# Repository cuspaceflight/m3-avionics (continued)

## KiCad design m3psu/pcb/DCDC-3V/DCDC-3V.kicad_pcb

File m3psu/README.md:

# Martlet 3 Power Supply Unit

The Power Supply Unit is designed to have current monitoring and control over every single power line (5V, 3.3V, and VBatt), and all can be controlled via an MCU. It has on-board Li-ion battery charging and balancing capability, and can automatically switch between external power and internal power (or be commanded to do so).

## Notes By Module

### General Notes

- Everything is designed to assume shore power of 11.5V to 14.5V, i.e. a 12V lead-acid (car) battery.
- Internal power supply is assumed to be 2 Li-ion cells, 3.5V-4.2V per cell giving 7V-8.4V internal supply.
- All components are designed to function at max working voltage of 16V, or higher (usually 25V where possible).
- 0402s are not available for capacitors >1µF and ≥16V.
    - Large capacitors will have to use the smallest footprint possible (which varies accordingly).
- All resistors are 0402s unless carrying large currents. Check power rating (in hidden field) if so.
    - Be cautious about resistors with values <100Ω since they're likely carrying large enough currents to be concerned about power.
- Assembled stack has to have charger board and controller board next to each other, followed by DC/DC converters as furthest.
- The I2C Bus is pulled up at the microcontroller unit.

### DC/DC Converter

- Choose: LTC3887 2475658(FAR).
- Max current provisioned: 1A @5V or @3.3V
- Operating Frequency: 575kHz.
- Choose Schottky diode to carry 1A (these are optional in the circuit, but increases efficiency)(choose: NSR20F30NXT5G (2317558(FAR)).
- Switching pair of totem pole N-MOSFETs (choose: SiZ340DT (2422226(FAR)).
- Boost capacitors are 100x total input (gate) capacitance of topside MOSFETs.
- Bigger inductors are better, but it's a compromise on space (choose: TYS5040100M-10 2292532(FAR) -> Iripple = 0.41A).
- Large filtering capacitors give low ripple voltage. (choose: GRM21BR61E226ME44L 1907510(FAR) -> Vripple = 1.2mV).
- Rsense at 50mΩ because Vsense max is 75mV and expected current ~1A (choose: LRCS0603-0R05FT5 1506129(FAR)).
- Filter over Isense is 2\*Cp\*Rs ≤ ESL/R (equivalent series inductance of sense resistor est. ~0.5nH).

#### Software Configurations

- Addresses are 0x40 to 0x45 (0b100 0000 X to 0b100 0101 X), note that the EEPROM is supposed to have the 3 most significant bits as 100 by default.
    - Address 0x40:
        - V0 = 5V Cameras (1A)
        - V1 = 3.3V Pyro µC (0.1A)
    - Address 0x41:
        - V0 = 5V Radio AMP (0.35A)
        - V1 = 3.3V Radio µC + etc (0.25A)
    - Address 0x42:
        - V0 = 5V AUX1 (1A)
        - V1 = 5V CAN transceivers (0.1A)
    - Address 0x43:
        - V0 = 5V IMU ADIS (0.3A)
        - V1 = 3.3V IMU µC + etc (0.3A)
    - Address 0x44:
        - V0 = 5V AUX2 (1A)
        - V1 = 3.3V Flight Computer µC + etc (0.15A)
    - Address 0x45:
        - V0 = 3.3V AUX1 (1A)
        - V1 = 3.3V Datalogger µC + etc (0.3A)
- Since external temp monitoring is not needed and shorted to GND, set the `UT_FAULT_LIMIT` to –275°C, `IOUT_CAL_GAIN_TC` to zero and the `UT_FAULT_RE-SPONSE` to ignore.
- The DC/DC converters start low, and must be configured with their voltages before turning them on.
- Use `PAGE` command to select channel 0/1/both for control over I2C.
- Set `ON_OFF_CONFIG` to `On_off_config_use_pmbus`.
- Send `OPERATION` command to turn channel on or off as needed.

### Lithium Battery Charger

- Choose: MAX17435 2516688(FAR).
- Address is 0x09 (0b000 1001 X).
- Charging current limit is set to 2.7A using the potential divider, with assumption that cells are 2.6Ah.
- Switching pair of totem pole N-MOSFETs (choose: SiZ340DT (2422226(FAR)), same as in the DC/DC Converter.
- The P-FET from the battery needs to have *very low* Rds-on for efficiency (choose: Si7157DP 2471947(FAR) it's big, but there's nothing smaller).
- P-FET from main power just needs to have low enough Rds-on to handle ~4A (choose: Si7101DN 2364059(FAR)). This is used to control whether the charger is actually charging.
- The two soft-start N-MOSFETs on the input need to withstand 3A current draw (choose: STL15DN4F5 2098274(FAR) it's also big, but is a pair).
- The reverse polarity protection(?) N-MOSFET can be as small as possible since it carries very little current (choose: PMZB150UNE 2498598(FAR)).
- Big inductor is needed for lower ripple current for more efficiency (choose: SRP5030T-4R7M 2309887(FAR) -> Iripple = 0.9A).
- Large input and output capacitance to stabilise circuit (choose: GRM32ER61C476ME15L 1735538(FAR)).
- ACIN limits are 11.5-14.5V using the potential divider, with assumption of a nominal source charging of 12V (lead-acid battery).

#### Software Considerations

- The charger has two "switches", one for enabling charging and monitoring of discharging, and the other to control if the charger is connected to the external power supply.
- By default, both are pulled down, and so must be set high for charging to begin.
- When switching from shore power to internal power before launch, disable the external power supply from the charger first, and then switch the whole stack using the dedicated power OR.
    - The reason is because the Lithium Charger does its *own* power OR-ing but isn't as fast, so just switching from the dedicated power OR causes the lithium charger to switch at the same time, causing the switchover time to be the slower of the 2 which is undesirable, and pointless.
- All digital inputs and outputs (apart from the Bus) are funneled through the port expander (see port expander for details).

##### Port Expander (for Lithium Charger)

- Choose: PCAL9538A 2428172(FAR).
- Address is 0x70 (0b111 0000 X).
- Ports P4-P7 are grounded to prevent floating, but datasheet advises to change them to outputs after bootup.

### Lithium Battery Bleeders

- The N-MOSFETs carries only small amounts of current and so can be very small (choose: PMZB150UNE 2498598(FAR)).
- The P-MOSFET carries only a small amount of current and so can be very small (choose: PMZB320UPE 2498601(FAR)).
- The bleed resistors have to take around 0.5W if they are 47Ω (choose: ERJP06F47R0V 1750737(FAR)).

### Lithium Battery Module

- This will use one of the global reserve lines for the middle battery tap, but will not be linked to the external lines. Note that this will break the global interconnection.

### Active Power ORing

- Choose: LTC4353 2115909(FAR).
- N-MOSFETs need to withstand 3A current draw (choose: STL15DN4F5 2098274(FAR)), same as in Lithium Battery Charger.
- Capacitors 10x the gate capacitance (Ciss) of the MOSFET that it is switching (choose: CGA2B3X7R1H223K050BB 2210825(FAR)).

### Pyro Channel Monitor and Control

- Choose: LTC4151 (2295457(FAR)).
- The P-MOSFETs that control the channel have to carry up to 2A each for short bursts (choose: CSD25310Q2 2501102(FAR)).
- The N-MOSFET that control the P-MOSFET only carries a small amount of current (choose: PMZB150UNE 2498598(FAR)), same as the Li-ion bleeders.

#### Software Configurations

- Address of Current Monitor is 0x6F (0b110 1111 X).
- The readout for the current is 0-81.92mV (20µV resolution) and must be converted to mA. With Rsense = 0.01Ω, range is 0-8A, with resolution of 2mA.
- The readout of the voltage is also the readout of the main line voltage (after the power OR).

### PSU for the PSU

- Choose: TPS61252 2382918(FAR).
- Max current provisioned: 0.2A @3.3V.
- Operatiing frequency: 1.25MHz.
- Choose smallest footprint inductor possible which meets requirements (choose: VLS201610HBX-3R3M-1 2455353(FAR)).
- Input-Output Capacitors are large for low ripple (choose: GRM21BR61E226ME44L 1907510(FAR)).

## List of Common Parts

### Capacitors (25V)

- 4µ7 - 2426959
- 1µ - 2218855

- 100n - 2496811

- 10n - 2210793

- 4n7 - 2496786
- 1n5 - 2210833

- 220p - 2210772
- 47p - 2210781

### Resistors (±1%)

- 2M - 1458762

- 150k - 2447110
- 100k - 2447094

- 56k - 2447198
- 33k - 2447160
- 30k1 - 2072900
- 24k9 - 1803690
- 23k2 - 2302774
- 15k8 - 2302757
- 10k - 2447096

- 7k32 - 2073231
- 6k2 - 2331559
- 5k76 - 1803113
- 5k1 - 2447201
- 4k99 - 1469715
- 4k7 - 2447187
- 4k32 - 2073037
- 3k57 - 2302693
- 1k96 - 1803065
- 1k - 2447120

- 100 - 2447095

- 50m - 1506129

## Notes on Routing

### Microcontroller Board

- I2C pins on:
    - 40,41,42 (SDA,SCL,SMBA) I2C(3)
    - 57,58,59 (SMBA,SCL,SDA) I2C(1)
    - 29,30,33 (SCL,SDA,SMBA) I2C(2)
- The various GPIOs have not been connected in the schematic yet, and hence will not show up on the routing. Route them last, since any GPIO port works.
- The bottom and left side of the microcontroller is mostly inaccessible using this layout.
- Note that the DCDC converter (3v3) operates at 1.25MHz, so keep it away from signal channels, and keep the components as tight as possible together.
- Shift the power OR a little more to the left (leave some room for the logic tracks). The top left dual MOSFET can go closer to the connector and northwards. The other dual MOSFET needs to be shifted down a little and left.
- VSHORE from the dual MOSFET should not cut across the large empty space on the right. (makes other things difficult to fit)

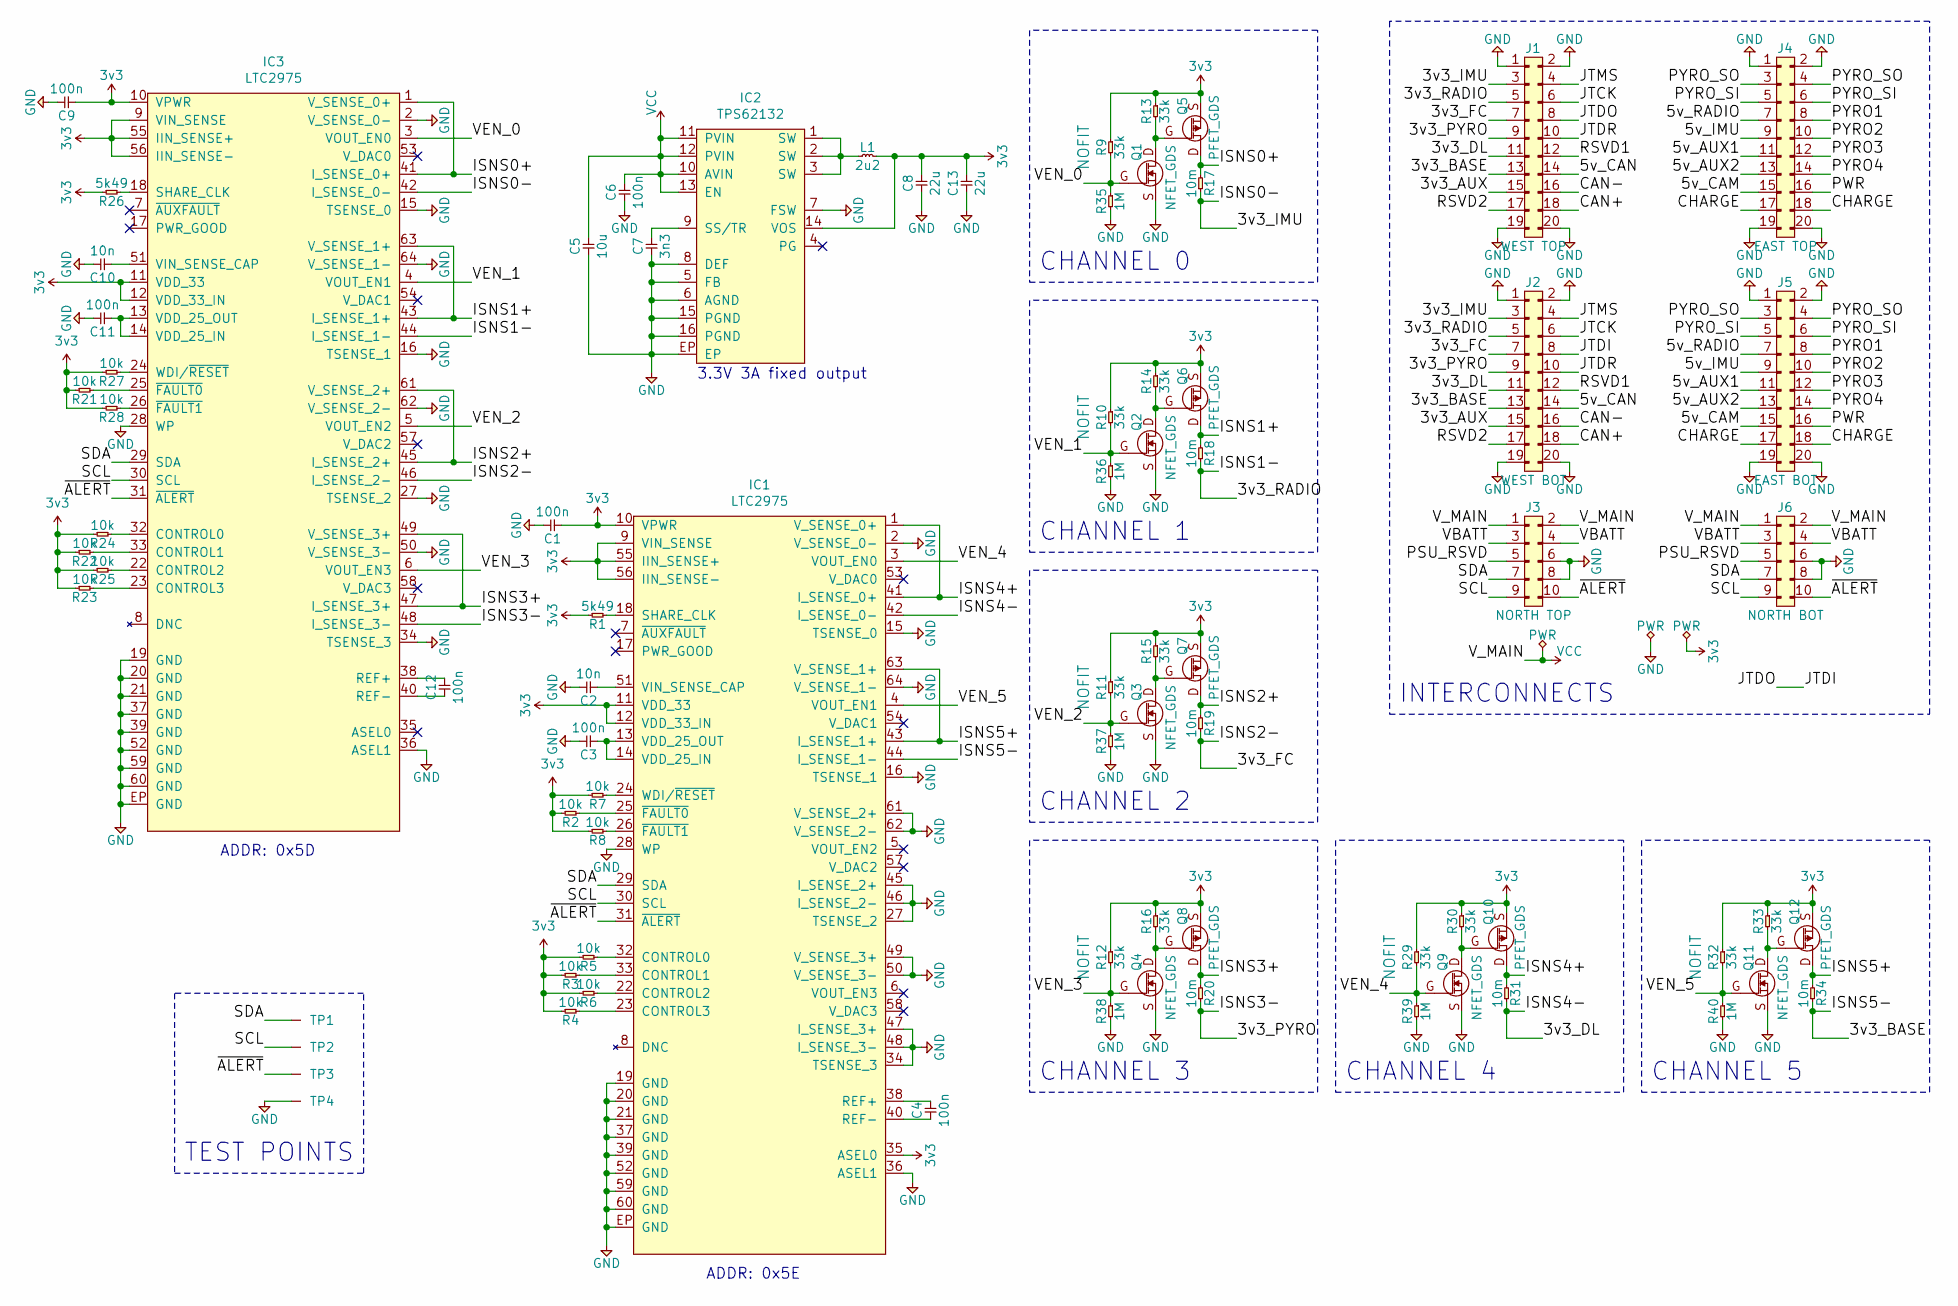
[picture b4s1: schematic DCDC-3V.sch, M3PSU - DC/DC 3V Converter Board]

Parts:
C1, C3, C4, C6, C9, C11, C12: 100n; 0402
C2, C10: 10n; 0402
C5: 10u; 0805
C7: 3n3; 0402
C8, C13: 22u; 0805
IC1, IC3: LTC2975; QFN-64-EP-LTC-UP; Farnell 2461150
IC2: TPS62132; QFN-16-EP-TI; Farnell 2492468
J1: WEST TOP; TFML-110-02-L-D
J2: WEST BOT; SFML-110-02-L-D-LC
J3: NORTH TOP; TFML-105-02-L-D
J4: EAST TOP; TFML-110-02-L-D
J5: EAST BOT; SFML-110-02-L-D-LC
J6: NORTH BOT; SFML-105-02-L-D-LC
L1: 2u2; XFL4020; Farnell 2289216
Q1, Q2, Q3, Q4, Q9, Q11: NFET_GDS; PowerPAK-SC-75-6L-Single; Farnell 2364070
Q5, Q6, Q7, Q8, Q10, Q12: PFET_GDS; SON2x2; Farnell 2501102
R1, R26: 5k49; 0402
R2, R3, R4, R5, R6, R7, R8, R21, R22, R23, R24, R25, R27, R28: 10k; 0402
R9, R10, R11, R12, R13, R14, R15, R16, R29, R30, R32, R33: 33k; 0402
R17, R18, R19, R20, R31, R34: 10m; 0603
R35, R36, R37, R38, R39, R40: 1M; 0402
TP1, TP2, TP3, TP4: TESTPAD

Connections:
3v3: C1.2, C8.1, C9.2, C13.1, IC1.9 (VIN_SENSE), IC1.10 (VPWR), IC1.11 (VDD_33), IC1.12 (VDD_33_IN), IC1.35 (ASEL0), IC1.55 (IIN_SENSE+), IC1.56 (IIN_SENSE-), IC2.14 (VOS), IC3.9 (VIN_SENSE), IC3.10 (VPWR), IC3.11 (VDD_33), IC3.12 (VDD_33_IN), IC3.55 (IIN_SENSE+), IC3.56 (IIN_SENSE-), L1.2, Q5.S, Q6.S, Q7.S, Q8.S, Q10.S, Q12.S, R1.1, R2.1, R3.1, R4.1, R5.1, R6.1, R7.1, R8.1, R9.1, R10.1, R11.1, R12.1, R13.1, R14.1, R15.1, R16.1, R21.1, R22.1, R23.1, R24.1, R25.1, R26.1, R27.1, R28.1, R29.1, R30.1, R32.1, R33.1
/3v3_AUX: J1.15, J2.15
/3v3_BASE: IC1.44 (I_SENSE_1-), J1.13, J2.13, R34.1
/3v3_DL: IC1.42 (I_SENSE_0-), J1.11, J2.11, R31.1
/3v3_FC: IC3.46 (I_SENSE_2-), J1.7, J2.7, R19.1
/3v3_IMU: IC3.42 (I_SENSE_0-), J1.3, J2.3, R17.1
/3v3_PYRO: IC3.48 (I_SENSE_3-), J1.9, J2.9, R20.1
/3v3_RADIO: IC3.44 (I_SENSE_1-), J1.5, J2.5, R18.1
/5v_AUX1: J4.11, J5.11
/5v_AUX2: J4.13, J5.13
/5v_CAM: J4.15, J5.15
/5v_CAN: J1.14, J2.14
/5v_IMU: J4.9, J5.9
/5v_RADIO: J4.7, J5.7
/CAN+: J1.18, J2.18
/CAN-: J1.16, J2.16
/CHARGE: J4.17, J4.18, J5.17, J5.18
/ISNS0+: IC3.1 (V_SENSE_0+), IC3.41 (I_SENSE_0+), Q5.D, R17.2
/ISNS1+: IC3.43 (I_SENSE_1+), IC3.63 (V_SENSE_1+), Q6.D, R18.2
/ISNS2+: IC3.45 (I_SENSE_2+), IC3.61 (V_SENSE_2+), Q7.D, R19.2
/ISNS3+: IC3.47 (I_SENSE_3+), IC3.49 (V_SENSE_3+), Q8.D, R20.2
/ISNS4+: IC1.1 (V_SENSE_0+), IC1.41 (I_SENSE_0+), Q10.D, R31.2
/ISNS5+: IC1.43 (I_SENSE_1+), IC1.63 (V_SENSE_1+), Q12.D, R34.2
/JTCK: J1.6, J2.6
/JTDI: J1.8, J2.8
/JTDR: J1.10, J2.10
/JTMS: J1.4, J2.4
/PSU_RSVD: J3.5, J6.5
/PWR: J4.16, J5.16
/PYRO1: J4.8, J5.8
/PYRO2: J4.10, J5.10
/PYRO3: J4.12, J5.12
/PYRO4: J4.14, J5.14
/PYRO_SI: J4.5, J4.6, J5.5, J5.6
/PYRO_SO: J4.3, J4.4, J5.3, J5.4
/RSVD1: J1.12, J2.12
/RSVD2: J1.17, J2.17
/SCL: IC1.30 (SCL), IC3.30 (SCL), J3.9, J6.9, TP2.1
/SDA: IC1.29 (SDA), IC3.29 (SDA), J3.7, J6.7, TP1.1
/VBATT: J3.3, J3.4, J6.3, J6.4
/VEN_0: IC3.3 (VOUT_EN0), Q1.G, R9.2, R35.1
/VEN_1: IC3.4 (VOUT_EN1), Q2.G, R10.2, R36.1
/VEN_2: IC3.5 (VOUT_EN2), Q3.G, R11.2, R37.1
/VEN_3: IC3.6 (VOUT_EN3), Q4.G, R12.2, R38.1
/VEN_4: IC1.3 (VOUT_EN0), Q9.G, R29.2, R39.1
/VEN_5: IC1.4 (VOUT_EN1), Q11.G, R32.2, R40.1
/~ALERT: IC1.31 (~ALERT), IC3.31 (~ALERT), J3.10, J6.10, TP3.1
GND: C1.1, C2.1, C3.1, C5.2, C6.2, C7.2, C8.2, C9.1, C10.1, C11.1, C13.2, IC1.2 (V_SENSE_0-), IC1.15 (TSENSE_0), IC1.16 (TSENSE_1), IC1.19 (GND), IC1.20 (GND), IC1.21 (GND), IC1.27 (TSENSE_2), IC1.28 (WP), IC1.34 (TSENSE_3), IC1.36 (ASEL1), IC1.37 (GND), IC1.39 (GND), IC1.45 (I_SENSE_2+), IC1.46 (I_SENSE_2-), IC1.47 (I_SENSE_3+), IC1.48 (I_SENSE_3-), IC1.49 (V_SENSE_3+), IC1.50 (V_SENSE_3-), IC1.52 (GND), IC1.59 (GND), IC1.60 (GND), IC1.61 (V_SENSE_2+), IC1.62 (V_SENSE_2-), IC1.64 (V_SENSE_1-), IC1.EP (GND), IC2.5 (FB), IC2.6 (AGND), IC2.7 (FSW), IC2.8 (DEF), IC2.15 (PGND), IC2.16 (PGND), IC2.EP, IC3.2 (V_SENSE_0-), IC3.15 (TSENSE_0), IC3.16 (TSENSE_1), IC3.19 (GND), IC3.20 (GND), IC3.21 (GND), IC3.27 (TSENSE_2), IC3.28 (WP), IC3.34 (TSENSE_3), IC3.36 (ASEL1), IC3.37 (GND), IC3.39 (GND), IC3.50 (V_SENSE_3-), IC3.52 (GND), IC3.59 (GND), IC3.60 (GND), IC3.62 (V_SENSE_2-), IC3.64 (V_SENSE_1-), IC3.EP (GND), J1.1, J1.2, J1.19, J1.20, J2.1, J2.2, J2.19, J2.20, J3.6, J3.8, J4.1, J4.2, J4.19, J4.20, J5.1, J5.2, J5.19, J5.20, J6.6, J6.8, Q1.S, Q2.S, Q3.S, Q4.S, Q9.S, Q11.S, R35.2, R36.2, R37.2, R38.2, R39.2, R40.2, TP4.1
unnamed: C2.2, IC1.51 (VIN_SENSE_CAP)
unnamed: C3.2, IC1.13 (VDD_25_OUT), IC1.14 (VDD_25_IN)
unnamed: C4.1, IC1.38 (REF+)
unnamed: C4.2, IC1.40 (REF-)
unnamed: C7.1, IC2.9 (SS/TR)
unnamed: C10.2, IC3.51 (VIN_SENSE_CAP)
unnamed: C11.2, IC3.13 (VDD_25_OUT), IC3.14 (VDD_25_IN)
unnamed: C12.1, IC3.38 (REF+)
unnamed: C12.2, IC3.40 (REF-)
unnamed: IC1.18 (SHARE_CLK), R1.2
unnamed: IC1.22 (CONTROL2), R6.2
unnamed: IC1.23 (CONTROL3), R4.2
unnamed: IC1.24 (WDI/~RESET), R7.2
unnamed: IC1.25 (~FAULT0), R2.2
unnamed: IC1.26 (~FAULT1), R8.2
unnamed: IC1.32 (CONTROL0), R5.2
unnamed: IC1.33 (CONTROL1), R3.2
unnamed: IC2.1 (SW), IC2.2 (SW), IC2.3 (SW), L1.1
unnamed: IC3.18 (SHARE_CLK), R26.2
unnamed: IC3.22 (CONTROL2), R25.2
unnamed: IC3.23 (CONTROL3), R23.2
unnamed: IC3.24 (WDI/~RESET), R27.2
unnamed: IC3.25 (~FAULT0), R21.2
unnamed: IC3.26 (~FAULT1), R28.2
unnamed: IC3.32 (CONTROL0), R24.2
unnamed: IC3.33 (CONTROL1), R22.2
unnamed: Q1.D, Q5.G, R13.2
unnamed: Q2.D, Q6.G, R14.2
unnamed: Q3.D, Q7.G, R15.2
unnamed: Q4.D, Q8.G, R16.2
unnamed: Q9.D, Q10.G, R30.2
unnamed: Q11.D, Q12.G, R33.2
VCC: C5.1, C6.1, IC2.10 (AVIN), IC2.11 (PVIN), IC2.12 (PVIN), IC2.13 (EN), J3.1, J3.2, J6.1, J6.2

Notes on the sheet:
INTERCONNECTS
ADDR: 0x5E
CHANNEL 0
CHANNEL 1
CHANNEL 2
CHANNEL 3
3.3V 3A fixed output
CHANNEL 4
CHANNEL 5
ADDR: 0x5D
TEST POINTS

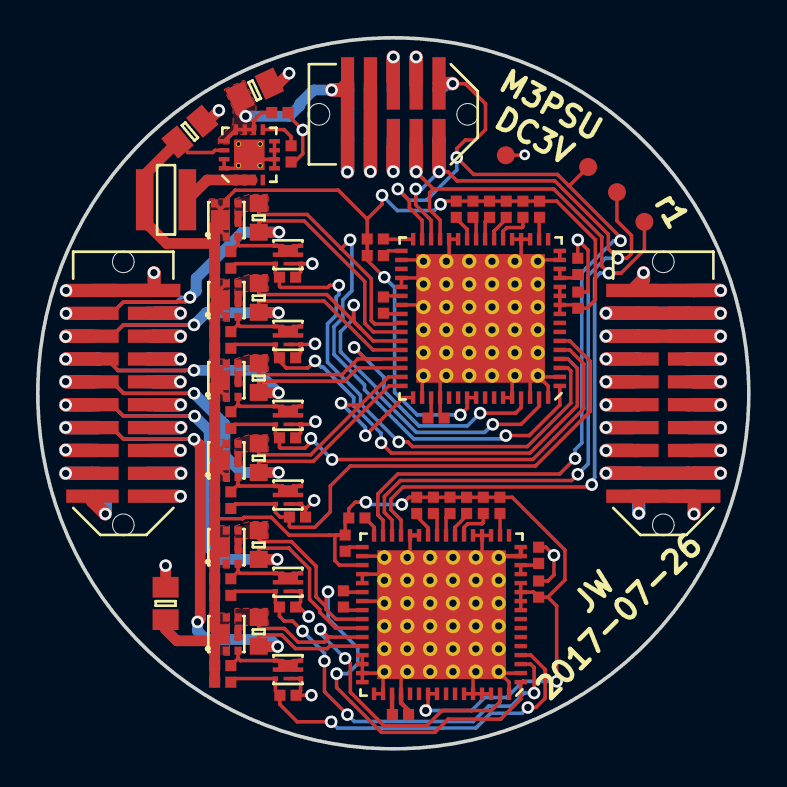
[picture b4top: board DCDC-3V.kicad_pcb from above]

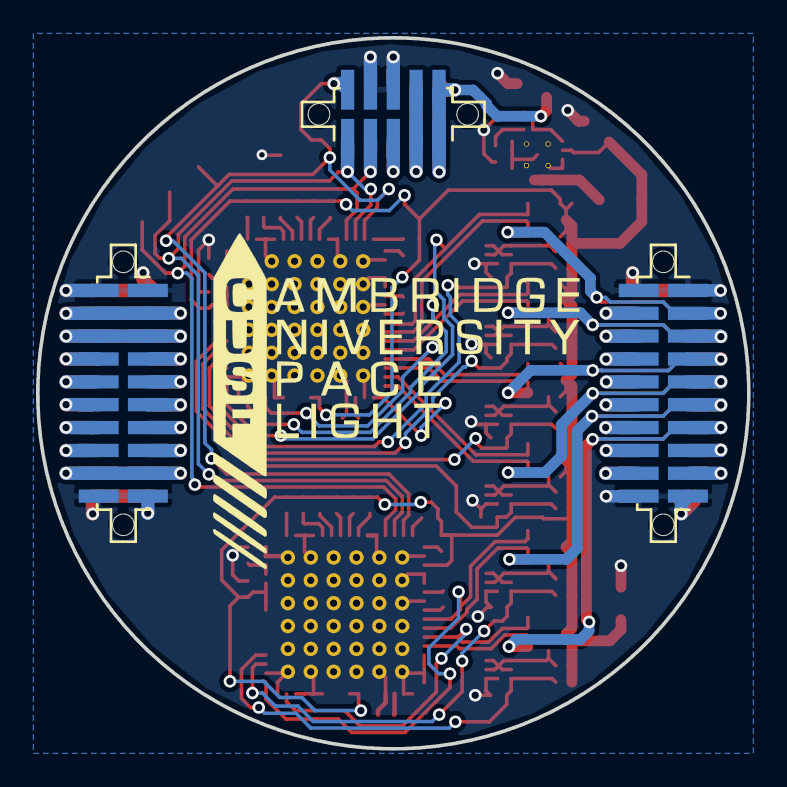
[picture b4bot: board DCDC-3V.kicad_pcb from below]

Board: 2 copper layers, 39.5 x 39.5 mm, 79 parts (3 on the bottom side), 81 nets.

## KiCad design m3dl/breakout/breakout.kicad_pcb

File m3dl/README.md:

# Martlet 3 Data Logger Stack

For overall BOM see: http://bit.ly/1YytYK4

x1 Temperature Sensor Board:
- LTC2983 10 Channel fancy box.
- 9 Thermocouples w/ Cold junction compensation.
- SPI over data logger stack interconnect (x4 Pins) plus interrupt.
- On board 18-pin connector (2 Pins per Thermocouple) connects to a wiring harness which passes through cutouts in below boards and breaks out to 9x 2-Pin in line connectors for thermocouples.

x2 Strain Gauge Boards:
- Analogue front end w/ AD8226.
- 3 Strain Gauges per PCB – 6 Total.
- Connection to ADC Inputs over data logger stack interconnect (x6 Pins).
- Per PCB 3 on board 4-pin connectors (1 per Gauge) connect to a wiring harness which passes through cutouts in below boards and breaks out to 6x 4-Pin in line connectors for strain gauges.

x1 Pressure Sensor Board:
- Absolute pressure sensors with mV Output to be placed externally.
- Simple RC filter connects sensor outputs to ADC over data logger stack interconnect (x5 Pins).
- Maximum 5 external Pressure Sensors .
- On board 10-pin connector to a cable which passes through cutouts in below boards and attaches to the external sensors through a wiring harness in a similar manner to the above.

x1 Main Board:
- 64 Pin STM32F405
- uSD Card
- CAN Controller
- Surface mount USB port for debugging

x1 Base JTAG & Connector Board:
- STM32F4 doing JTAG to USB and CAN to USB simultaneous
- JST-PA Connectors for USB, Pyro, Power/Charge, ARM and CAMERA.

20 Pin Data Logger Interconnect: 
 - x5 SPI 
 - x5 ADC Pressure 
 - x6 ADC Strain 
 - x4 GND

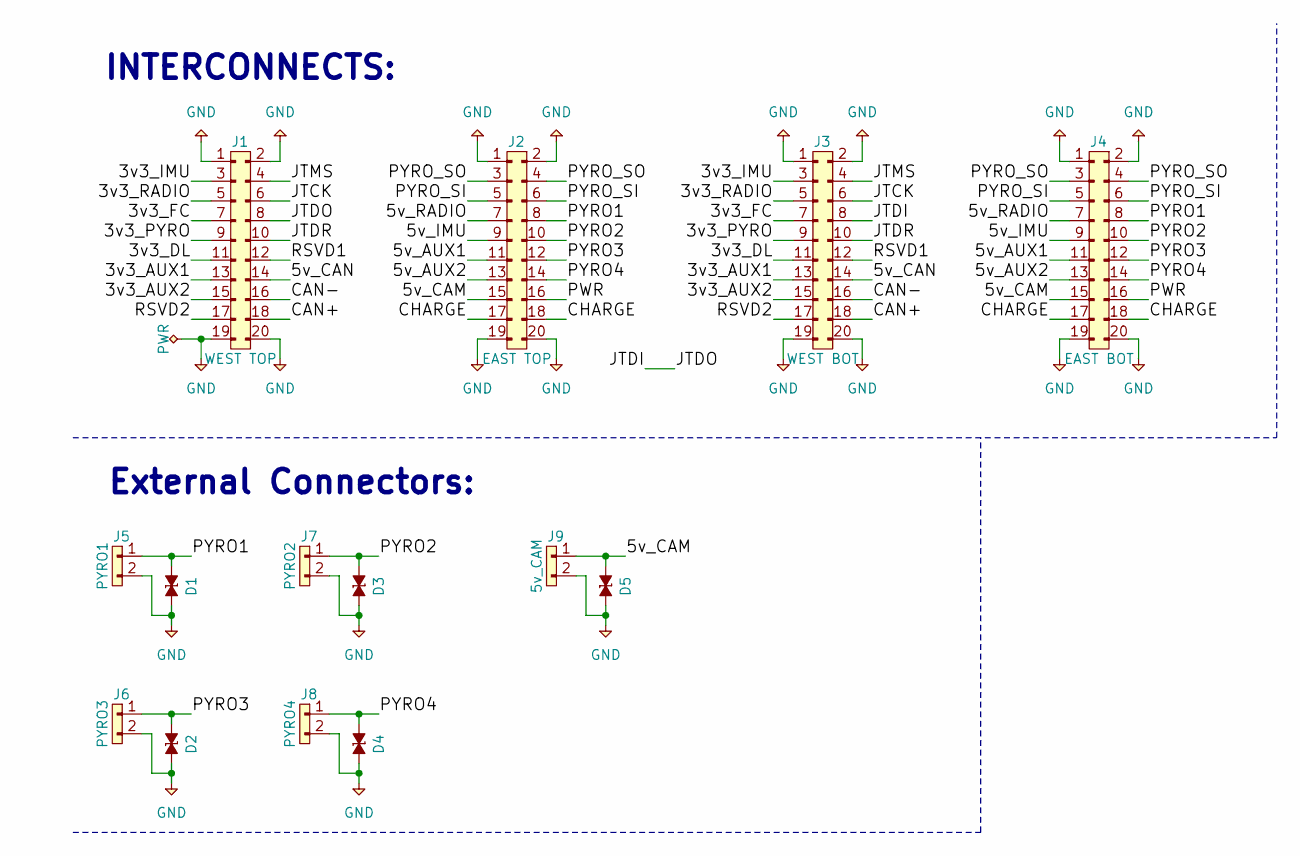
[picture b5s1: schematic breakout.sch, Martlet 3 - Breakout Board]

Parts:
D1, D2, D3, D4, D5: ESD_DIODE; 0402; Farnell 2368169
J1: WEST TOP; TFML-110-02-L-D
J2: EAST TOP; TFML-110-02-L-D
J3: WEST BOT; SFML-110-02-L-D-LC
J4: EAST BOT; SFML-110-02-L-D-LC
J5: PYRO1; S2B-EH
J6: PYRO3; S2B-EH
J7: PYRO2; S2B-EH
J8: PYRO4; S2B-EH
J9: 5v_CAM; S2B-EH

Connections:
/3v3_AUX1: J1.13, J3.13
/3v3_AUX2: J1.15, J3.15
/3v3_DL: J1.11, J3.11
/3v3_FC: J1.7, J3.7
/3v3_IMU: J1.3, J3.3
/3v3_PYRO: J1.9, J3.9
/3v3_RADIO: J1.5, J3.5
/5v_AUX1: J2.11, J4.11
/5v_AUX2: J2.13, J4.13
/5v_CAM: D5.1, J2.15, J4.15, J9.1
/5v_CAN: J1.14, J3.14
/5v_IMU: J2.9, J4.9
/5v_RADIO: J2.7, J4.7
/CAN+: J1.18, J3.18
/CAN-: J1.16, J3.16
/CHARGE: J2.17, J2.18, J4.17, J4.18
/JTCK: J1.6, J3.6
/JTDI: J1.8, J3.8
/JTDR: J1.10, J3.10
/JTMS: J1.4, J3.4
/PWR: J2.16, J4.16
/PYRO1: D1.1, J2.8, J4.8, J5.1
/PYRO2: D3.1, J2.10, J4.10, J7.1
/PYRO3: D2.1, J2.12, J4.12, J6.1
/PYRO4: D4.1, J2.14, J4.14, J8.1
/PYRO_SI: J2.5, J2.6, J4.5, J4.6
/PYRO_SO: J2.3, J2.4, J4.3, J4.4
/RSVD1: J1.12, J3.12
/RSVD2: J1.17, J3.17
GND: D1.2, D2.2, D3.2, D4.2, D5.2, J1.1, J1.2, J1.19, J1.20, J2.1, J2.2, J2.19, J2.20, J3.1, J3.2, J3.19, J3.20, J4.1, J4.2, J4.19, J4.20, J5.2, J6.2, J7.2, J8.2, J9.2

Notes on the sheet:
INTERCONNECTS:
External Connectors:

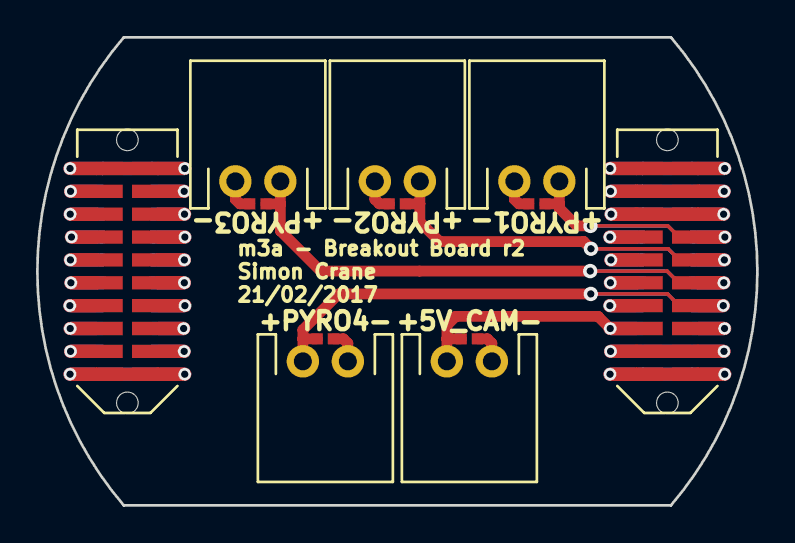
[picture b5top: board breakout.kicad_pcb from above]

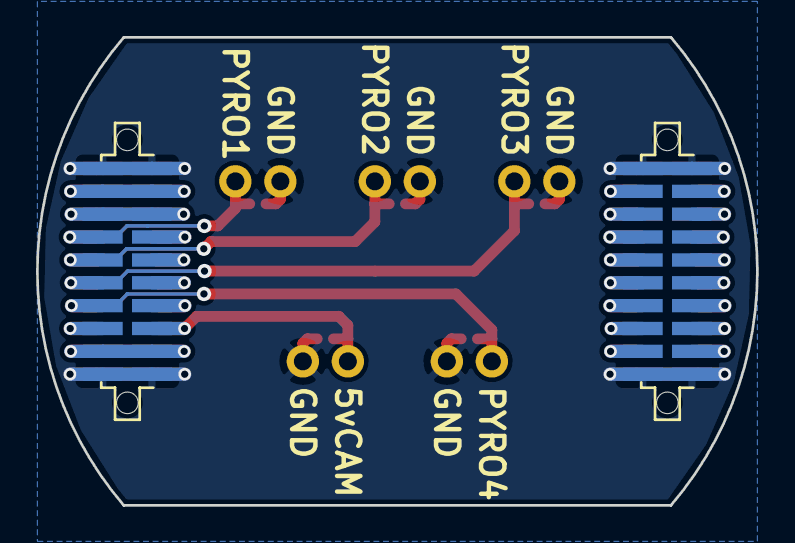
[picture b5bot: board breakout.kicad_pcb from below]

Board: 2 copper layers, 40.0 x 26.0 mm, 14 parts (2 on the bottom side), 30 nets.

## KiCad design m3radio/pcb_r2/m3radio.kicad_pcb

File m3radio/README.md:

# Martlet 3 Radio

Datasheets:
[GPS ublox max-7q]: https://www.u-blox.com/sites/default/files/products/documents/MAX7-NEO7_HIM_(UBX-13003704).pdf
[Radio SI4460]: https://www.silabs.com/Support%20Documents/TechnicalDocs/Si4464-63-61-60.pdf

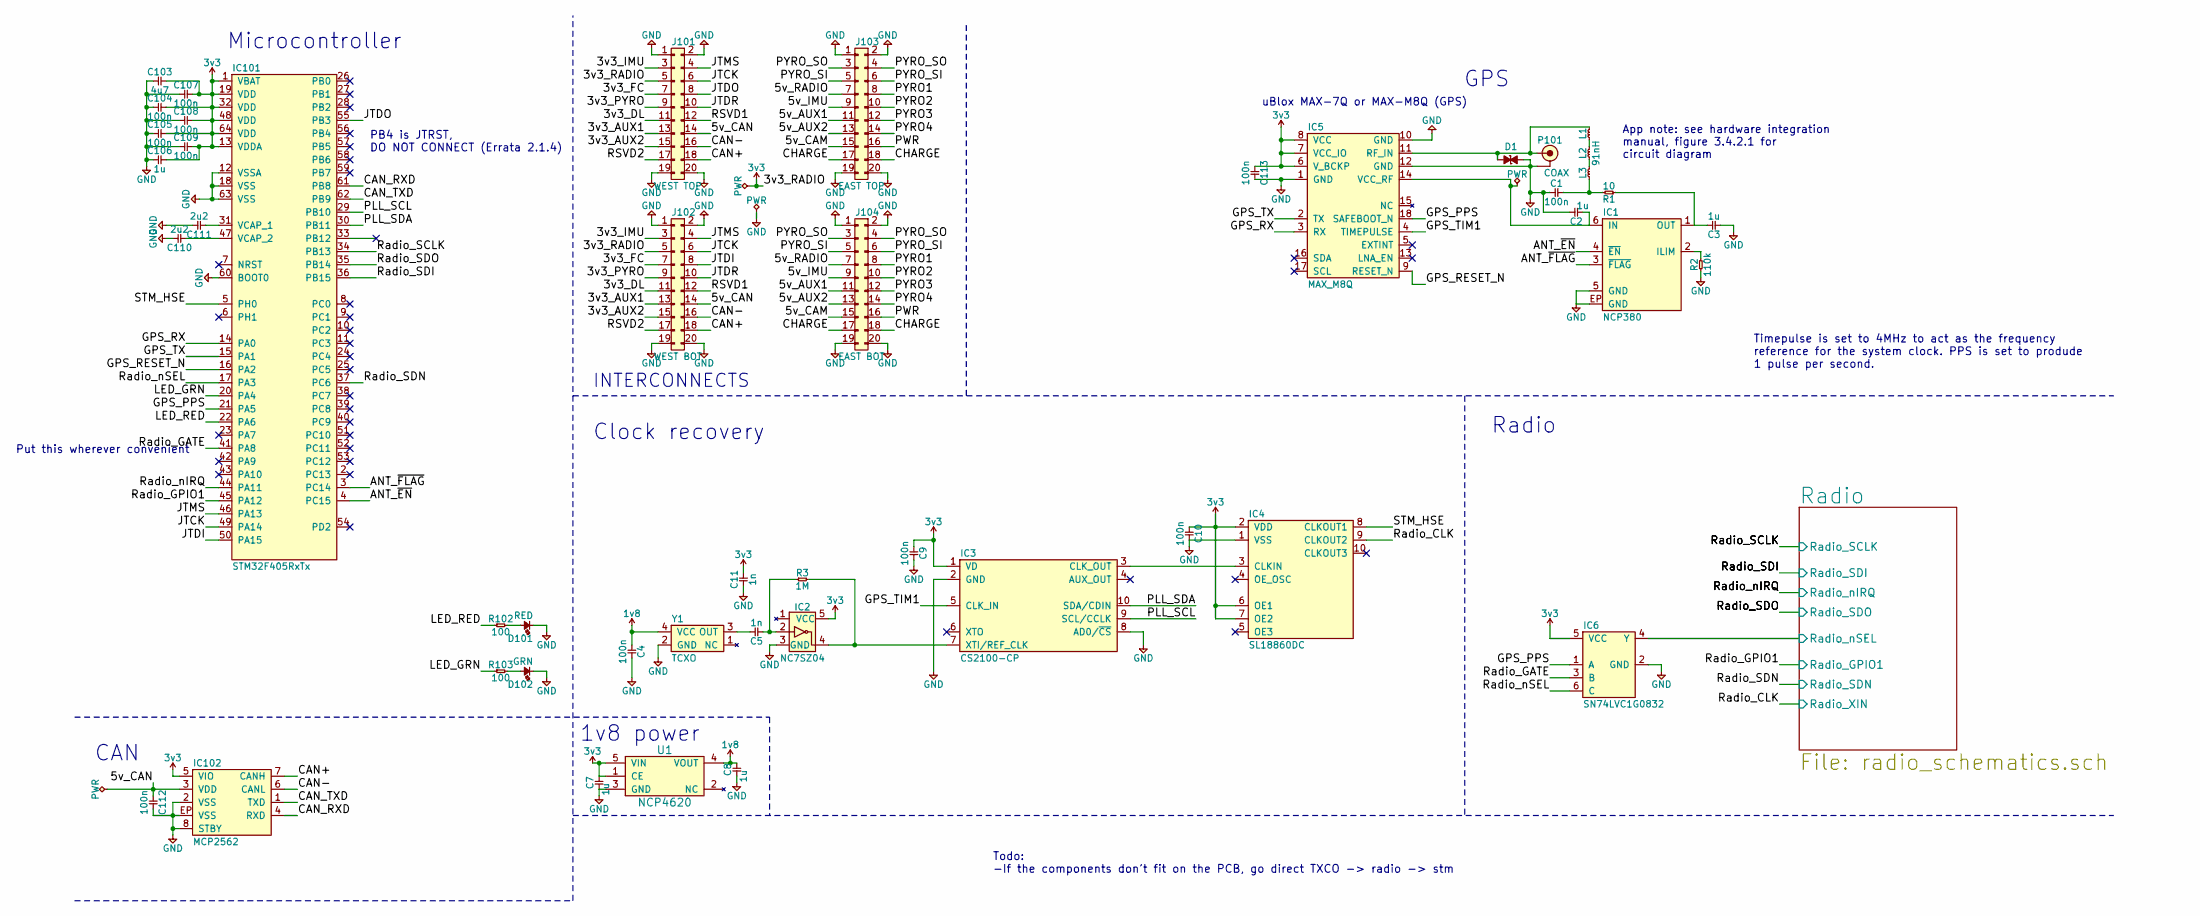
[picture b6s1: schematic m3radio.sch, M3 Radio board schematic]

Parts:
C1, C4, C9, C10, C104, C105, C107, C108, C109, C112, C113: 100n; 0402; Farnell 2496771
C2, C3, C7, C8, C106: 1u; 0402; Farnell 2496814
C5, C11: 1n; 0402; Farnell 2495166
C103: 4u7; 0402; Farnell 2426952
C110, C111: 2u2; 0402; Farnell 2362088
D1: ESD_DIODE; 0402; Farnell 2368169
D101: RED; 0603-LED; Farnell 2314404
D102: GRN; 0603-LED; Farnell 2290363
IC1: NCP380; DFN-6-EP-ONSEMI; Farnell 2464412
IC2: NC7SZ04; SOT-23-5; Farnell 1417667
IC3: CS2100-CP; MSOP-10; Mouser 777-CS2100CP-CZZ
IC4: SL18860DC; DFN-10-SL18860DC; Mouser 634-SL18860DC
IC5: MAX_M8Q; MAX-M8Q
IC6: SN74LVC1G0832; SC-70-6; Farnell 2406965
IC101: STM32F405RxTx; LQFP-64; Farnell 2064363
IC102: MCP2562; DFN-8-EP-MICROCHIP; Farnell 2448755
J101: WEST TOP; TFML-110-02-L-D
J102: WEST BOT; SFML-110-02-L-D-LC
J103: EAST TOP; TFML-110-02-L-D
J104: EAST BOT; SFML-110-02-L-D-LC
L1, L2, L3: 91nH; 0402-L; Farnell 2470339
P101: COAX; U.FL-R-SMT-1; Farnell 3908021
R1: 10; 0603; Farnell 1738878
R2: 110k; 0402; Farnell 2502502
R3: 1M; 0402; Farnell 2502805
R102, R103: 100; 0402; Farnell 9239111
U1: NCP4620; SC-70-5; Farnell 2464259
Y1: TCXO; TG-5006CG; Farnell 2405785

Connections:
1v8: C4.1, C8.2, U1.4 (VOUT), Y1.4 (VCC)
3v3: C7.2, C9.1, C10.1, C11.2, C103.2, C104.2, C105.2, C106.2, C107.2, C108.2, C109.2, C113.1, IC2.5 (VCC), IC3.1 (VD), IC4.2 (VDD), IC4.6 (OE1), IC4.7 (OE2), IC5.6 (V_BCKP), IC5.7 (VCC_IO), IC5.8 (VCC), IC6.5 (VCC), IC101.1 (VBAT), IC101.13 (VDDA), IC101.19 (VDD), IC101.32 (VDD), IC101.48 (VDD), IC101.64 (VDD), IC102.5 (VIO), J101.5, J102.5, U1.1 (CE), U1.5 (VIN); also elsewhere on the board
/3v3_AUX1: J101.13, J102.13
/3v3_AUX2: J101.15, J102.15
/3v3_DL: J101.11, J102.11
/3v3_FC: J101.7, J102.7
/3v3_IMU: J101.3, J102.3
/3v3_PYRO: J101.9, J102.9
/5v_AUX1: J103.11, J104.11
/5v_AUX2: J103.13, J104.13
/5v_CAM: J103.15, J104.15
/5v_CAN: C112.1, IC102.3 (VDD), J101.14, J102.14
/5v_IMU: J103.9, J104.9
/5v_RADIO: J103.7, J104.7
/ANT_~EN: IC1.4 (~EN), IC101.4 (PC15)
/ANT_~FLAG: IC1.3 (~FLAG), IC101.3 (PC14)
/CAN+: IC102.7 (CANH), J101.18, J102.18
/CAN-: IC102.6 (CANL), J101.16, J102.16
/CAN_RXD: IC101.61 (PB8), IC102.4 (RXD)
/CAN_TXD: IC101.62 (PB9), IC102.1 (TXD)
/CHARGE: J103.17, J103.18, J104.17, J104.18
/GPS_PPS: IC5.18 (SAFEBOOT_N), IC6.1 (A), IC101.21 (PA5)
/GPS_RESET_N: IC5.9 (RESET_N), IC101.16 (PA2)
/GPS_RX: IC5.3 (RX), IC101.14 (PA0)
/GPS_TIM1: IC3.5 (CLK_IN), IC5.4 (TIMEPULSE)
/GPS_TX: IC5.2 (TX), IC101.15 (PA1)
/JTCK: IC101.49 (PA14), J101.6, J102.6
/JTDI: IC101.50 (PA15), J102.8
/JTDO: IC101.55 (PB3), J101.8
/JTDR: J101.10, J102.10
/JTMS: IC101.46 (PA13), J101.4, J102.4
/LED_GRN: IC101.20 (PA4), R103.1
/LED_RED: IC101.22 (PA6), R102.1
/PLL_SCL: IC3.9 (SCL/CCLK), IC101.29 (PB10)
/PLL_SDA: IC3.10 (SDA/CDIN), IC101.30 (PB11)
/PWR: J103.16, J104.16
/PYRO1: J103.8, J104.8
/PYRO2: J103.10, J104.10
/PYRO3: J103.12, J104.12
/PYRO4: J103.14, J104.14
/PYRO_SI: J103.5, J103.6, J104.5, J104.6
/PYRO_SO: J103.3, J103.4, J104.3, J104.4
/RSVD1: J101.12, J102.12
/RSVD2: J101.17, J102.17
/Radio/Radio_nSEL: IC6.4 (Y); also elsewhere on the board
/Radio_CLK: IC4.9 (CLKOUT2); also elsewhere on the board
/Radio_GATE: IC6.3 (B), IC101.41 (PA8)
/Radio_GPIO1: IC101.45 (PA12); also elsewhere on the board
/Radio_SCLK: IC101.34 (PB13); also elsewhere on the board
/Radio_SDI: IC101.36 (PB15); also elsewhere on the board
/Radio_SDN: IC101.37 (PC6); also elsewhere on the board
/Radio_SDO: IC101.35 (PB14); also elsewhere on the board
/Radio_nIRQ: IC101.44 (PA11); also elsewhere on the board
/Radio_nSEL: IC6.6 (C), IC101.17 (PA3)
/STM_HSE: IC4.8 (CLKOUT1), IC101.5 (PH0)
GND: C1.1, C2.2, C3.1, C4.2, C7.1, C8.1, C9.2, C10.2, C11.1, C103.1, C104.1, C105.1, C106.1, C107.1, C108.1, C109.1, C110.2, C111.2, C112.2, C113.2, D1.2, D101.1, D102.1, IC1.5 (GND), IC1.EP (GND), IC2.3 (GND), IC3.2 (GND), IC3.8 (AD0/~CS), IC4.1 (VSS), IC5.1 (GND), IC5.10 (GND), IC5.12 (GND), IC6.2 (GND), IC101.12 (VSSA), IC101.18 (VSS), IC101.60 (BOOT0), IC101.63 (VSS), IC102.2 (VSS), IC102.8 (STBY), IC102.EP (VSS), J101.1, J101.2, J101.19, J101.20, J102.1, J102.2, J102.19, J102.20, J103.1, J103.2, J103.19, J103.20, J104.1, J104.2, J104.19, J104.20, P101.2 (GND), R2.1, U1.3 (GND), Y1.2 (GND); also elsewhere on the board
unnamed: C1.2, L3.1, R1.2
unnamed: C2.1, IC1.6 (IN), IC5.14 (VCC_RF)
unnamed: C3.2, IC1.1 (OUT), R1.1
unnamed: C5.1, IC2.2, R3.1
unnamed: C5.2, Y1.3 (OUT)
unnamed: C110.1, IC101.47 (VCAP_2)
unnamed: C111.1, IC101.31 (VCAP_1)
unnamed: D1.1, IC5.11 (RF_IN), L1.2, P101.1 (RF)
unnamed: D101.2, R102.2
unnamed: D102.2, R103.2
unnamed: IC1.2 (ILIM), R2.2
unnamed: IC2.4, IC3.7 (XTI/REF_CLK), R3.2
unnamed: IC3.3 (CLK_OUT), IC4.3 (CLKIN)
unnamed: L1.1, L2.2
unnamed: L2.1, L3.2

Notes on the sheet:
CAN
Microcontroller
Radio
GPS
uBlox MAX-7Q or MAX-M8Q (GPS)
INTERCONNECTS
PB4 is JTRST, DO NOT CONNECT (Errata 2.1.4)
App note: see hardware integration manual, figure 3.4.2.1 for circuit diagram
1v8 power
Clock recovery
Todo: -If the components don't fit on the PCB, go direct TXCO -> radio -> stm
Put this wherever convenient
Timepulse is set to 4MHz to act as the frequency reference for the system clock. PPS is set to produde 1 pulse per second.

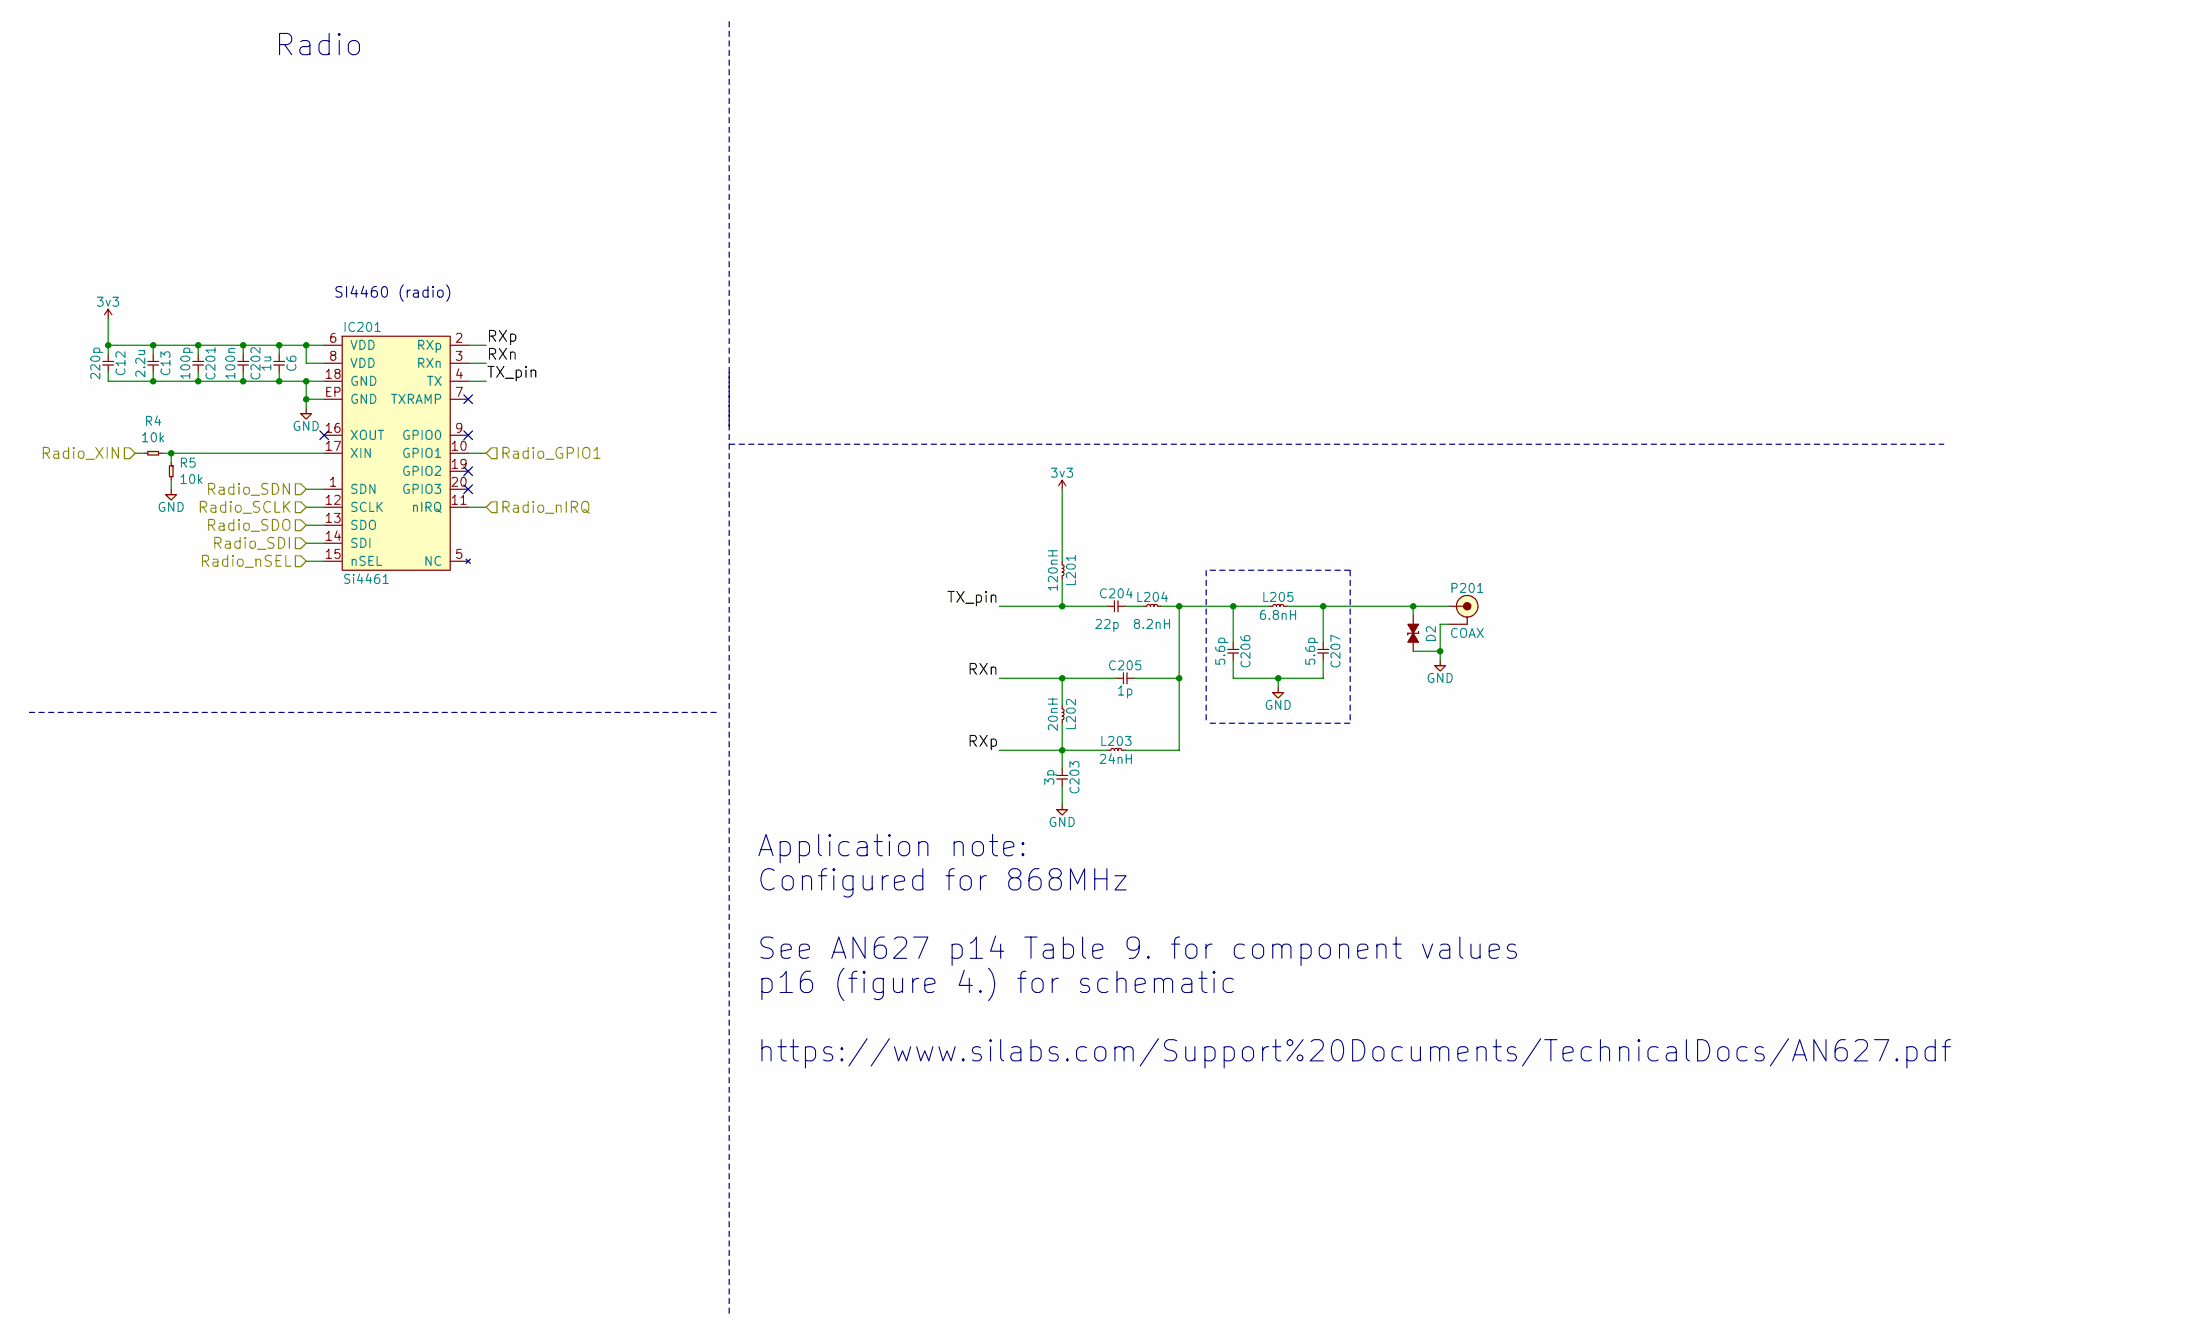
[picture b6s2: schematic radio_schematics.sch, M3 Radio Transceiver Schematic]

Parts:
C6: 1u; 0402; Farnell 2496814
C12: 220p; 0402; Farnell 2496800
C13: 2.2u; 0402; Farnell 2456102
C201: 100p; 0402; Farnell 2496792
C202: 100n; 0402; Farnell 2496771
C203: 3p; 0402; Farnell 2524984
C204: 22p; 0402; Farnell 1885344
C205: 1p; 0402; Farnell 2133992
C206, C207: 5.6p; 0402; Farnell 2310316
D2: ESD_DIODE; 0402; Farnell 2368169
IC201: Si4461; QFN-20-EP-SI; Farnell 2462636
L201: 120nH; 0603-L; Farnell 1865812
L202: 20nH; 0402; Farnell 1748728
L203: 24nH; 0402; Farnell 2470344
L204: 8.2nH; 0603-L; Farnell 6581778
L205: 6.8nH; 0402; Farnell 1762612
P201: COAX; U.FL-R-SMT-1; Farnell 3908021
R4, R5: 10k; 0402; Farnell 2379805

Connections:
3v3: C6.1, C12.1, C13.1, C201.1, C202.1, IC201.6 (VDD), IC201.8 (VDD), L201.1; also elsewhere on the board
/Radio/RXn: C205.1, IC201.3 (RXn), L202.1
/Radio/RXp: C203.1, IC201.2 (RXp), L202.2, L203.1
/Radio/Radio_nSEL: IC201.15 (nSEL); also elsewhere on the board
/Radio/TX_pin: C204.1, IC201.4 (TX), L201.2
/Radio_CLK: R4.1; also elsewhere on the board
/Radio_GPIO1: IC201.10 (GPIO1); also elsewhere on the board
/Radio_SCLK: IC201.12 (SCLK); also elsewhere on the board
/Radio_SDI: IC201.14 (SDI); also elsewhere on the board
/Radio_SDN: IC201.1 (SDN); also elsewhere on the board
/Radio_SDO: IC201.13 (SDO); also elsewhere on the board
/Radio_nIRQ: IC201.11 (nIRQ); also elsewhere on the board
GND: C6.2, C12.2, C13.2, C201.2, C202.2, C203.2, C206.2, C207.2, D2.2, IC201.18 (GND), IC201.EP (GND), P201.2 (GND), R5.2; also elsewhere on the board
unnamed: C204.2, L204.1
unnamed: C205.2, C206.1, L203.2, L204.2, L205.1
unnamed: C207.1, D2.1, L205.2, P201.1 (RF)
unnamed: IC201.17 (XIN), R4.2, R5.1

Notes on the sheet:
SI4460 (radio)
Radio
Application note: Configured for 868MHz See AN627 p14 Table 9. for component values p16 (figure 4.) for schematic https://www.silabs.com/Support%20Documents/TechnicalDocs/AN627.pdf
